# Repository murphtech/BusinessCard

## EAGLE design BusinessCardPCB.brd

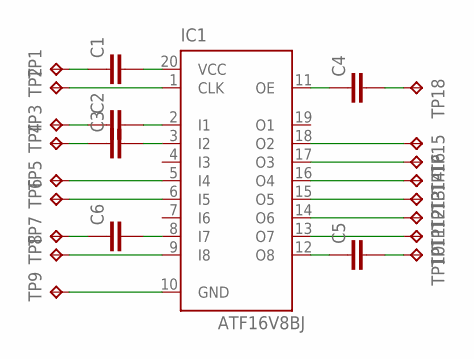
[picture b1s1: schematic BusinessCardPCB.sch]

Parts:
C1, C2, C3, C4, C5, C6: C-EUC0603K; C0603K
IC1: ATF16V8BJ; PLCC20
TP1, TP2, TP3, TP4, TP5, TP6, TP7, TP8, TP9, TP10, TP11, TP12, TP13, TP14, TP15, TP16, TP18: TPTP10R; TP10R

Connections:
unnamed: C1.1, TP1.TP
unnamed: C1.2, IC1.20 (VCC)
unnamed: IC1.1 (CLK), TP2.TP
unnamed: C2.1, TP3.TP
unnamed: C2.2, IC1.2 (I1)
unnamed: C3.2, IC1.3 (I2)
unnamed: C3.1, TP4.TP
unnamed: IC1.5 (I4), TP5.TP
unnamed: C6.2, IC1.8 (I7)
unnamed: C6.1, TP7.TP
unnamed: IC1.6 (I5), TP6.TP
unnamed: IC1.9 (I8), TP8.TP
unnamed: IC1.10 (GND), TP9.TP
unnamed: C5.1, IC1.12 (O8)
unnamed: C5.2, TP10.TP
unnamed: IC1.13 (O7), TP11.TP
unnamed: IC1.14 (O6), TP12.TP
unnamed: IC1.15 (O5), TP13.TP
unnamed: IC1.16 (O4), TP14.TP
unnamed: IC1.17 (O3), TP16.TP
unnamed: IC1.18 (O2), TP15.TP
unnamed: C4.1, IC1.11 (OE)
unnamed: C4.2, TP18.TP

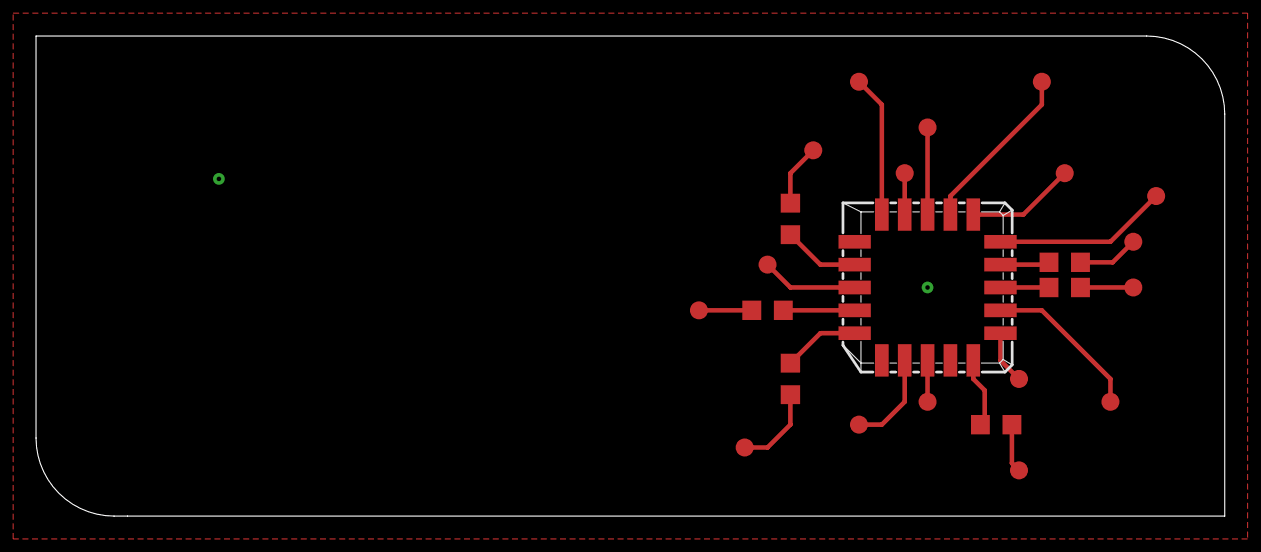
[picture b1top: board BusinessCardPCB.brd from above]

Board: 2 copper layers, 66.0 x 26.7 mm, 24 parts (0 on the bottom side), 23 nets.

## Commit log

2018-10-23 Adding first commit of business card
